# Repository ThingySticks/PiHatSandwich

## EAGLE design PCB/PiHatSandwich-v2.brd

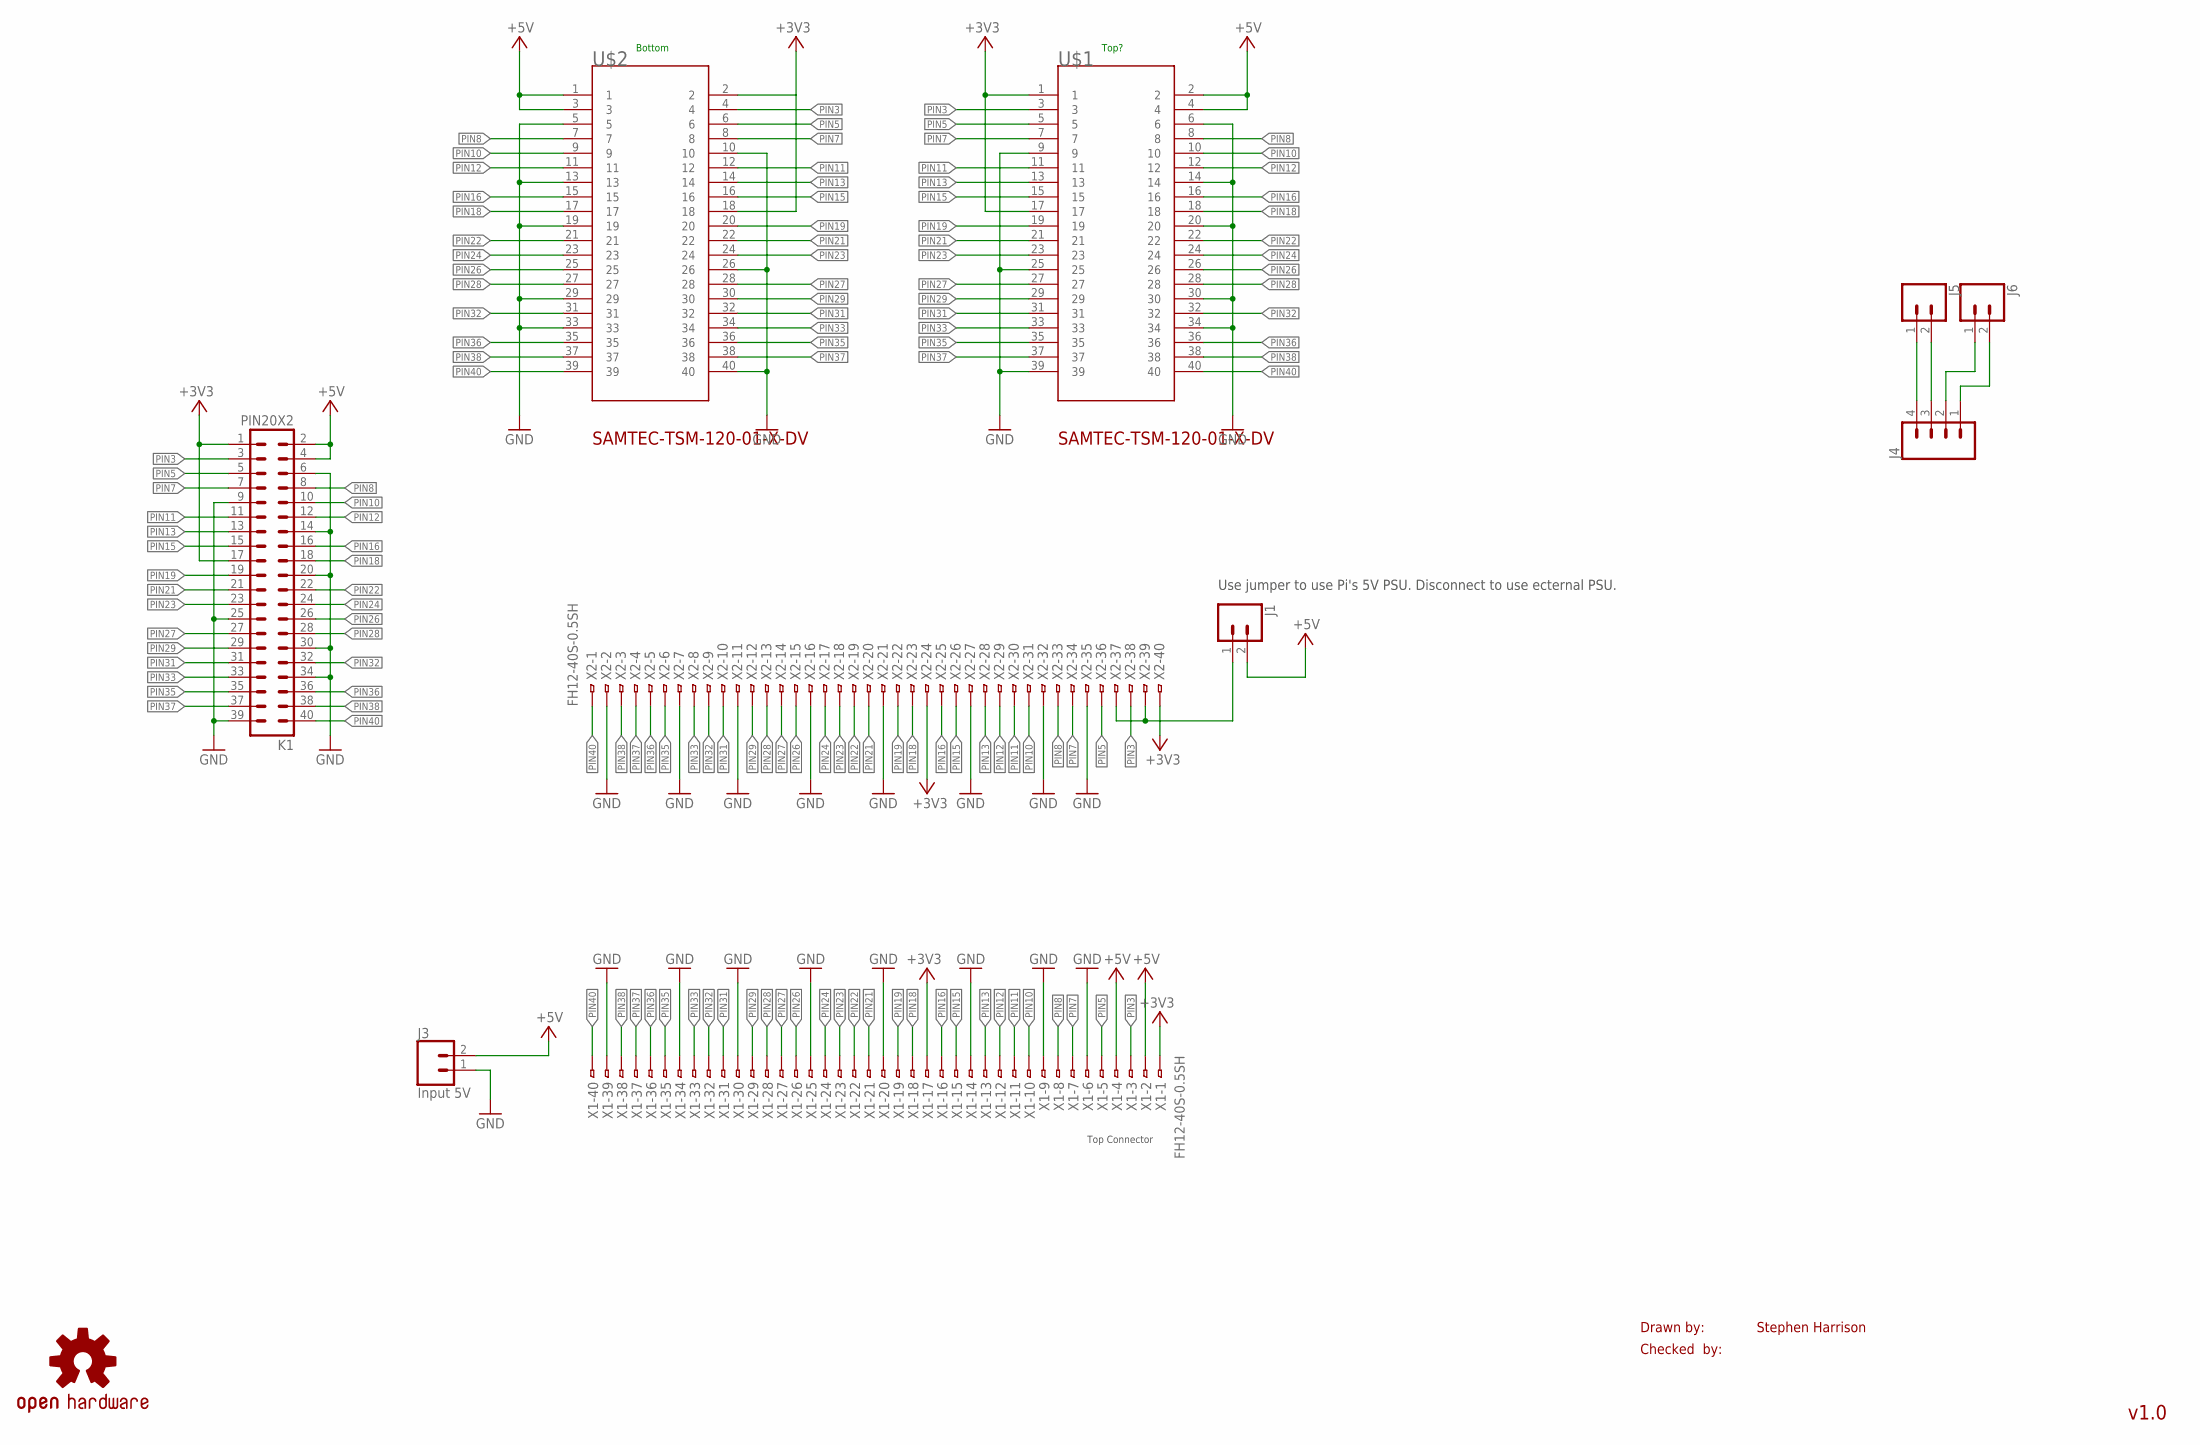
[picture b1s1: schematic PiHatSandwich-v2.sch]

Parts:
J1, J5, J6: CONN_02; 1X02
J3: Input 5V; MOLEX-1X2
J4: CONN_04POLAR; MOLEX-1X4
K1: PIN20X2; PIN_20X2
LOGO1: OSHW-LOGOL; OSHW-LOGO-L
U$1, U$2: SAMTEC-TSM-120-01-X-DVJ; SAMTEC-TSM-120-01-X-DV
X1, X2: FH12-40S-0.5SH

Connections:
+3V3: K1.1, K1.17, U$1.1, U$1.17, U$2.2, U$2.18, X1.1, X1.17, X2.24, X2.40
+5V: J1.2, J3.2, K1.2, K1.4, U$1.2, U$1.4, U$2.1, U$2.3, X1.2, X1.4
GND: J3.1, K1.6, K1.9, K1.14, K1.20, K1.25, K1.30, K1.34, K1.39, U$1.6, U$1.9, U$1.14, U$1.20, U$1.25, U$1.30, U$1.34, U$1.39, U$2.5, U$2.10, U$2.13, U$2.19, U$2.26, U$2.29, U$2.33, U$2.40, X1.6, X1.9, X1.14, X1.20, X1.25, X1.30, X1.34, X1.39, X2.2, X2.7, X2.11, X2.16, X2.21, X2.27, X2.32, X2.35
unnamed: J1.1, X2.37, X2.39
unnamed: J4.4, J5.1
unnamed: J4.3, J5.2
unnamed: J4.1, J6.2
unnamed: J4.2, J6.1
PIN3: K1.3, U$1.3, U$2.4, X1.3, X2.38
PIN5: K1.5, U$1.5, U$2.6, X1.5, X2.36
PIN7: K1.7, U$1.7, U$2.8, X1.7, X2.34
PIN8: K1.8, U$1.8, U$2.7, X1.8, X2.33
PIN10: K1.10, U$1.10, U$2.9, X1.10, X2.31
PIN11: K1.11, U$1.11, U$2.12, X1.11, X2.30
PIN12: K1.12, U$1.12, U$2.11, X1.12, X2.29
PIN13: K1.13, U$1.13, U$2.14, X1.13, X2.28
PIN15: K1.15, U$1.15, U$2.16, X1.15, X2.26
PIN16: K1.16, U$1.16, U$2.15, X1.16, X2.25
PIN18: K1.18, U$1.18, U$2.17, X1.18, X2.23
PIN19: K1.19, U$1.19, U$2.20, X1.19, X2.22
PIN21: K1.21, U$1.21, U$2.22, X1.21, X2.20
PIN22: K1.22, U$1.22, U$2.21, X1.22, X2.19
PIN23: K1.23, U$1.23, U$2.24, X1.23, X2.18
PIN24: K1.24, U$1.24, U$2.23, X1.24, X2.17
PIN26: K1.26, U$1.26, U$2.25, X1.26, X2.15
PIN27: K1.27, U$1.27, U$2.28, X1.27, X2.14
PIN28: K1.28, U$1.28, U$2.27, X1.28, X2.13
PIN29: K1.29, U$1.29, U$2.30, X1.29, X2.12
PIN31: K1.31, U$1.31, U$2.32, X1.31, X2.10
PIN32: K1.32, U$1.32, U$2.31, X1.32, X2.9
PIN33: K1.33, U$1.33, U$2.34, X1.33, X2.8
PIN35: K1.35, U$1.35, U$2.36, X1.35, X2.6
PIN36: K1.36, U$1.36, U$2.35, X1.36, X2.5
PIN37: K1.37, U$1.37, U$2.38, X1.37, X2.4
PIN38: K1.38, U$1.38, U$2.37, X1.38, X2.3
PIN40: K1.40, U$1.40, U$2.39, X1.40, X2.1

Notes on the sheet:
Drawn by:
Checked by:
Stephen Harrison
v1.0
Top Connector
Top?
Bottom
Use jumper to use Pi's 5V PSU. Disconnect to use ecternal PSU.

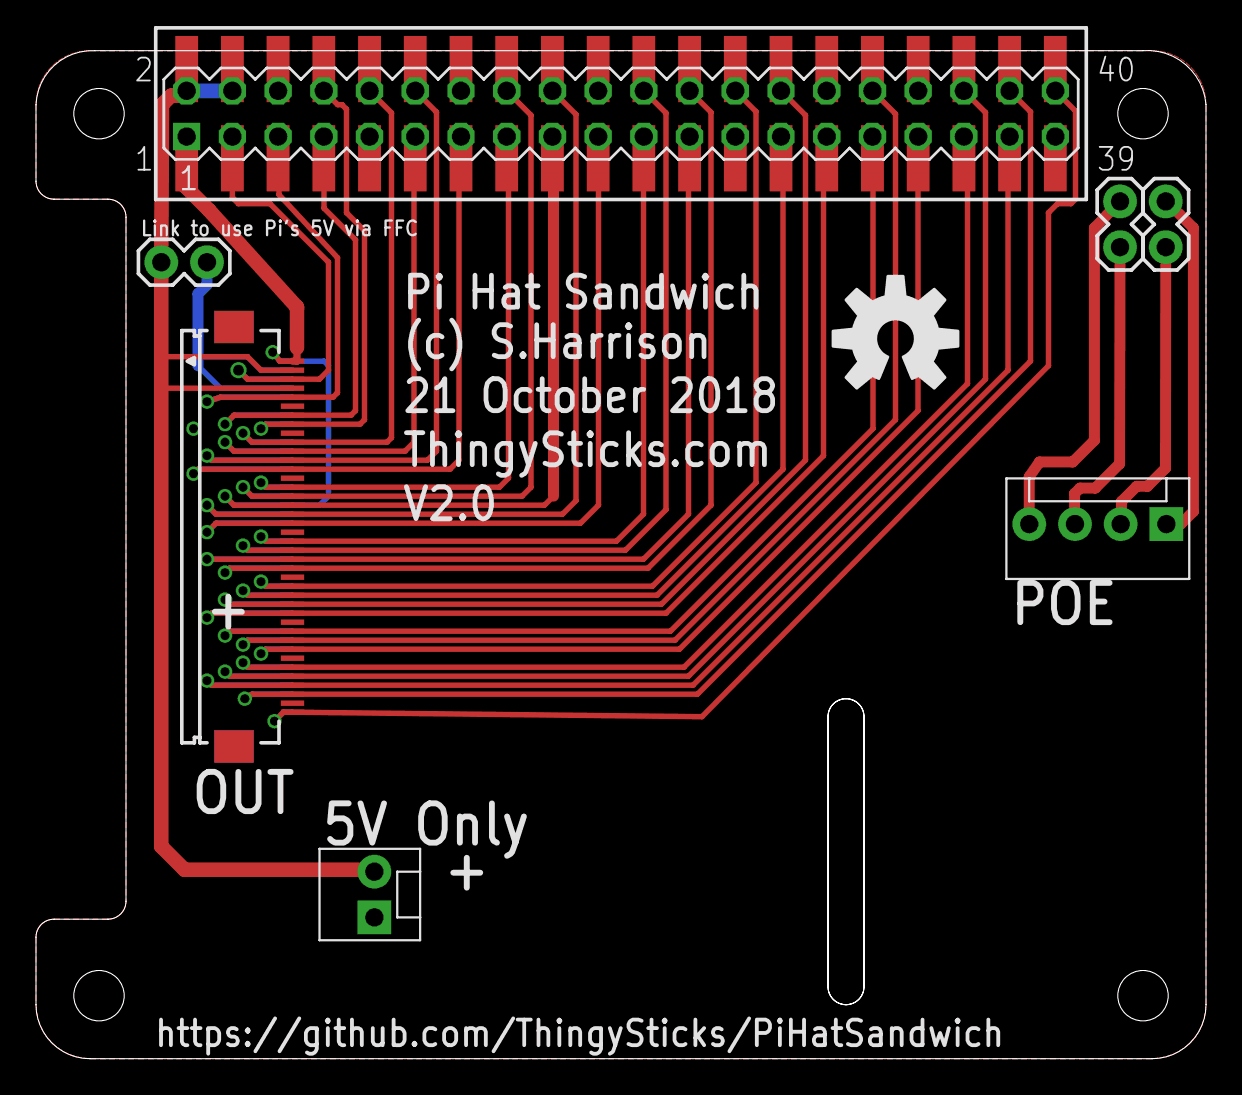
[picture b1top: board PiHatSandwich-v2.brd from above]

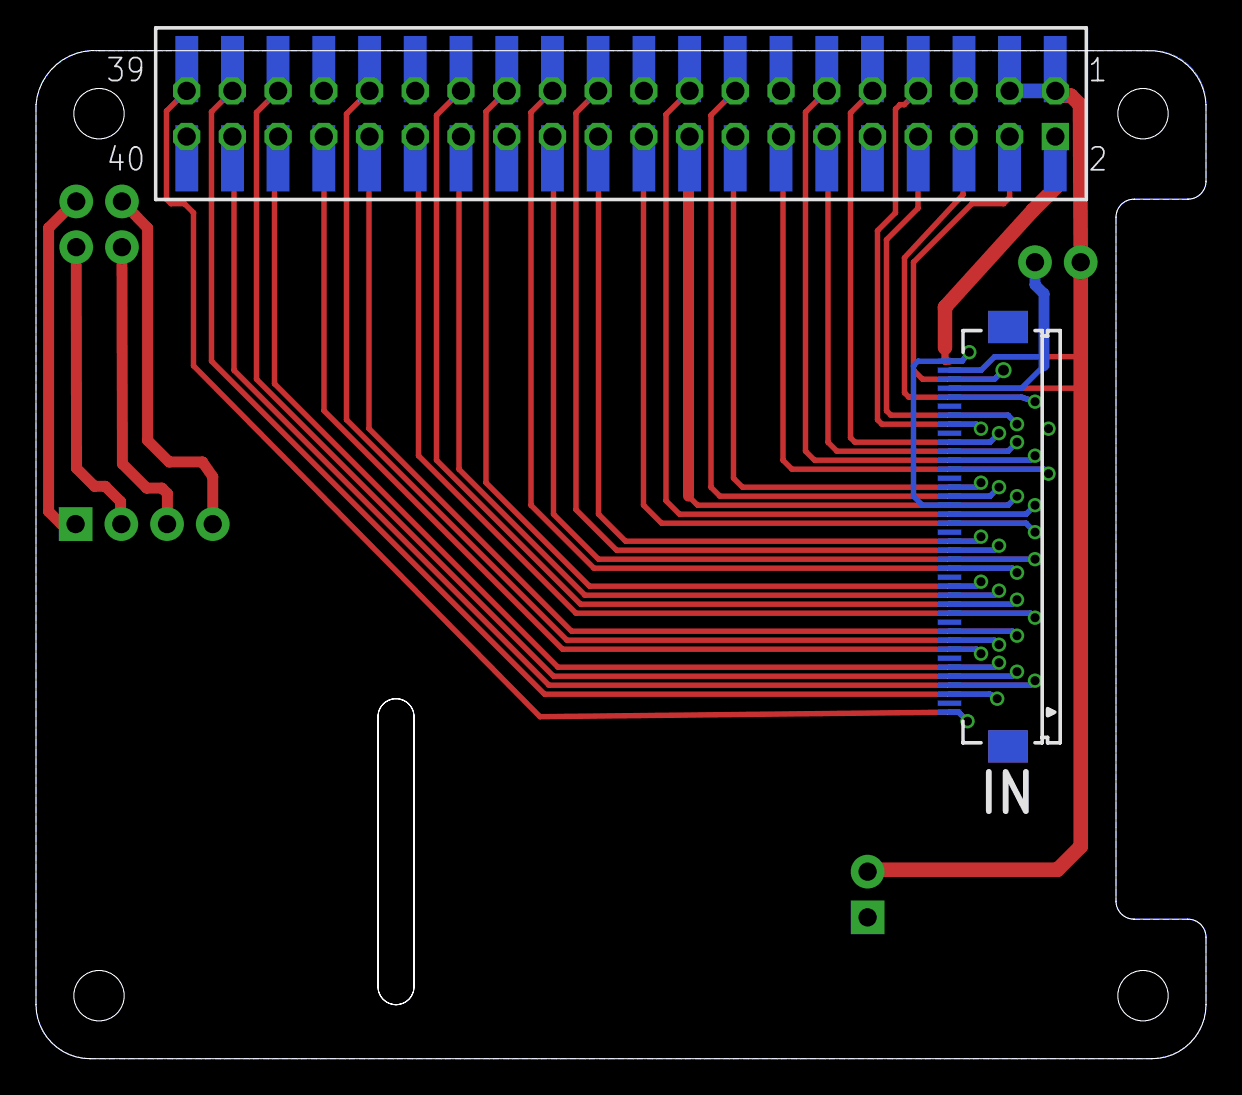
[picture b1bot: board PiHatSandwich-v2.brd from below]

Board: 2 copper layers, 65.0 x 56.0 mm, 11 parts (2 on the bottom side), 36 nets.

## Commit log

2018-10-20 Initial version as sent to DirtyPCBs
2018-10-21 Added v2 where the cable uses the far end to go up to other hats, the POE card has a nice large coutaway that helps.

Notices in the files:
parts and their libraries:
SparkFun-Connectors: Licensing: Creative Commons ShareAlike 4.0 International - https://creativecommons.org/licenses/by-sa/4.0
